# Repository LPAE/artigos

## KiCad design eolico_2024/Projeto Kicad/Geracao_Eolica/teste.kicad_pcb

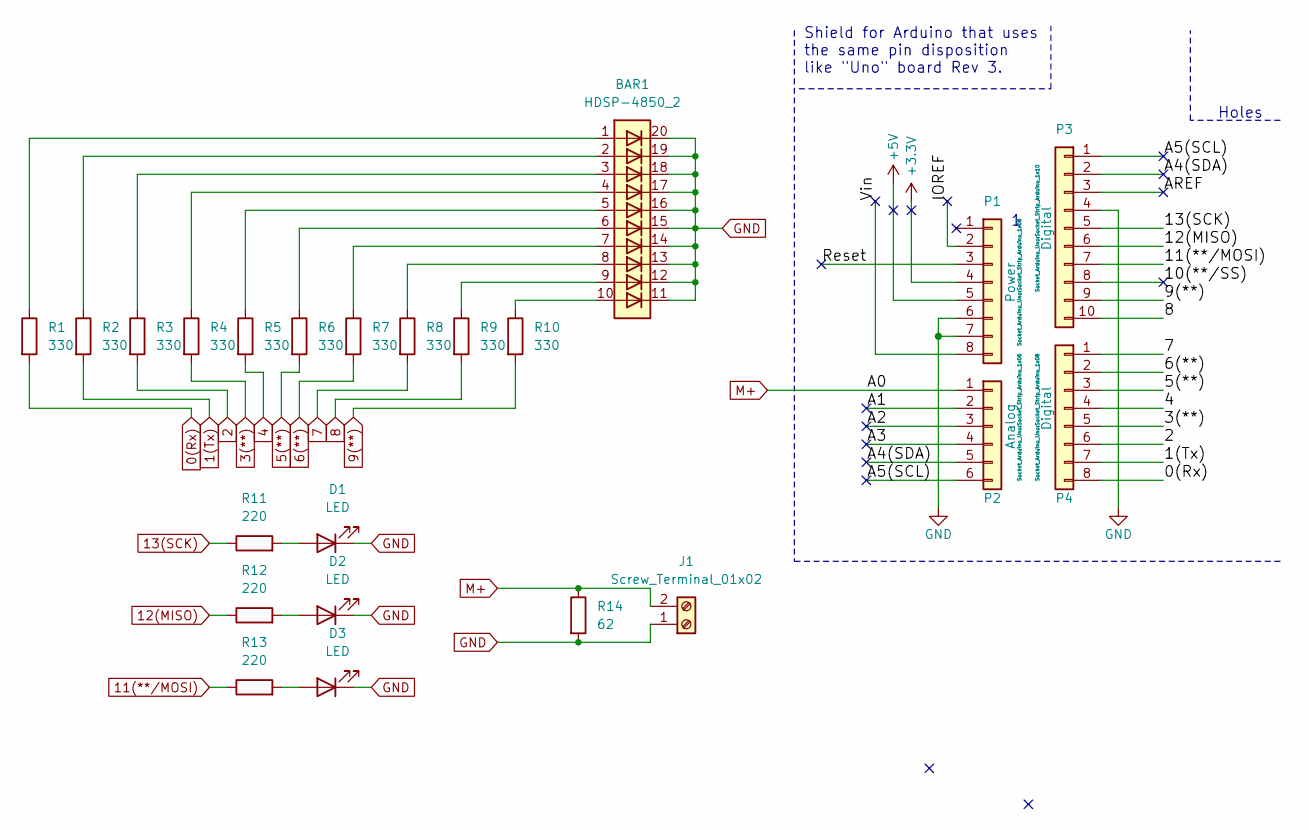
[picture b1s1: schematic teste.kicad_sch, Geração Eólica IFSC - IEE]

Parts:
BAR1: HDSP-4850_2; HDSP-4850
D1, D2, D3: LED; LED_D3.0mm
J1: Screw_Terminal_01x02; TerminalBlock_Phoenix_MKDS-1,5-2_1x02_P5.00mm_Horizontal
P1: Power; Socket_Strip_Arduino_1x08
P2: Analog; Socket_Strip_Arduino_1x06
P3: Digital; Socket_Strip_Arduino_1x10
P4: Digital; Socket_Strip_Arduino_1x08
R1, R2, R3, R4, R5, R6, R7, R8, R9, R10: 330; R_Axial_DIN0207_L6.3mm_D2.5mm_P10.16mm_Horizontal
R11, R12, R13: 220; R_Axial_DIN0207_L6.3mm_D2.5mm_P10.16mm_Horizontal
R14: 62; R_Axial_DIN0204_L3.6mm_D1.6mm_P7.62mm_Horizontal

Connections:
0(Rx): P4.8, R1.2
1(Tx): P4.7, R2.2
2: P4.6, R3.2
3(**): P4.5, R4.2
4: P4.4, R5.2
5(**): P4.3, R6.2
6(**): P4.2, R7.2
7: P4.1, R8.2
8: P3.10, R9.2
9(**): P3.9, R10.2
11(**/MOSI): P3.7, R13.1
12(MISO): P3.6, R12.1
13(SCK): P3.5, R11.1
+3V3: P1.4
+5V: P1.5
/10(**/SS): P3.8
/A1: P2.2
/A2: P2.3
/A3: P2.4
/A4(SDA): P2.5, P3.2
/A5(SCL): P2.6, P3.1
/AREF: P3.3
/IOREF: P1.2
/Reset: P1.3
/Vin: P1.8
GND: BAR1.11 (K), BAR1.12 (K), BAR1.13 (K), BAR1.14 (K), BAR1.15 (K), BAR1.16 (K), BAR1.17 (K), BAR1.18 (K), BAR1.19 (K), BAR1.20 (K), D1.1 (K), D2.1 (K), D3.1 (K), J1.1, P1.6, P1.7, P3.4, R14.2
M+: J1.2, P2.1, R14.1
unnamed: BAR1.1 (A), R1.1
unnamed: BAR1.2 (A), R2.1
unnamed: BAR1.3 (A), R3.1
unnamed: BAR1.4 (A), R4.1
unnamed: BAR1.5 (A), R5.1
unnamed: BAR1.6 (A), R6.1
unnamed: BAR1.7 (A), R7.1
unnamed: BAR1.8 (A), R8.1
unnamed: BAR1.9 (A), R9.1
unnamed: BAR1.10 (A), R10.1
unnamed: D1.2 (A), R11.2
unnamed: D2.2 (A), R12.2
unnamed: D3.2 (A), R13.2

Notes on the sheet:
Holes
Shield for Arduino that uses the same pin disposition like "Uno" board Rev 3.

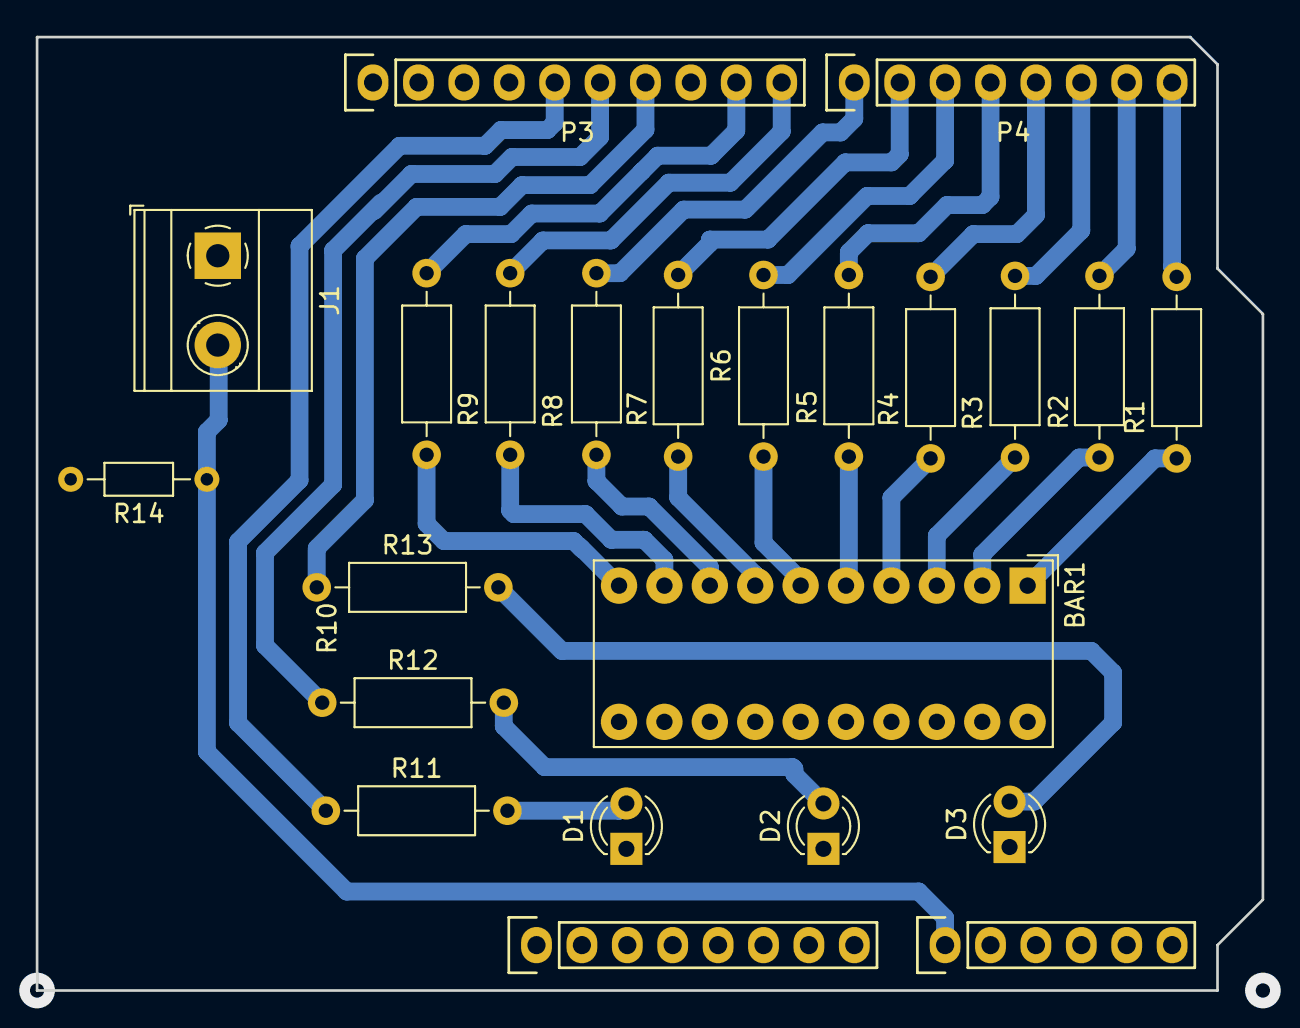
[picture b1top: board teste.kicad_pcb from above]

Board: 2 copper layers, 68.6 x 53.3 mm, 23 parts (0 on the bottom side), 30 nets.

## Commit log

2024-05-15 Adicionado arquivos
2024-05-15 Removido pasta
